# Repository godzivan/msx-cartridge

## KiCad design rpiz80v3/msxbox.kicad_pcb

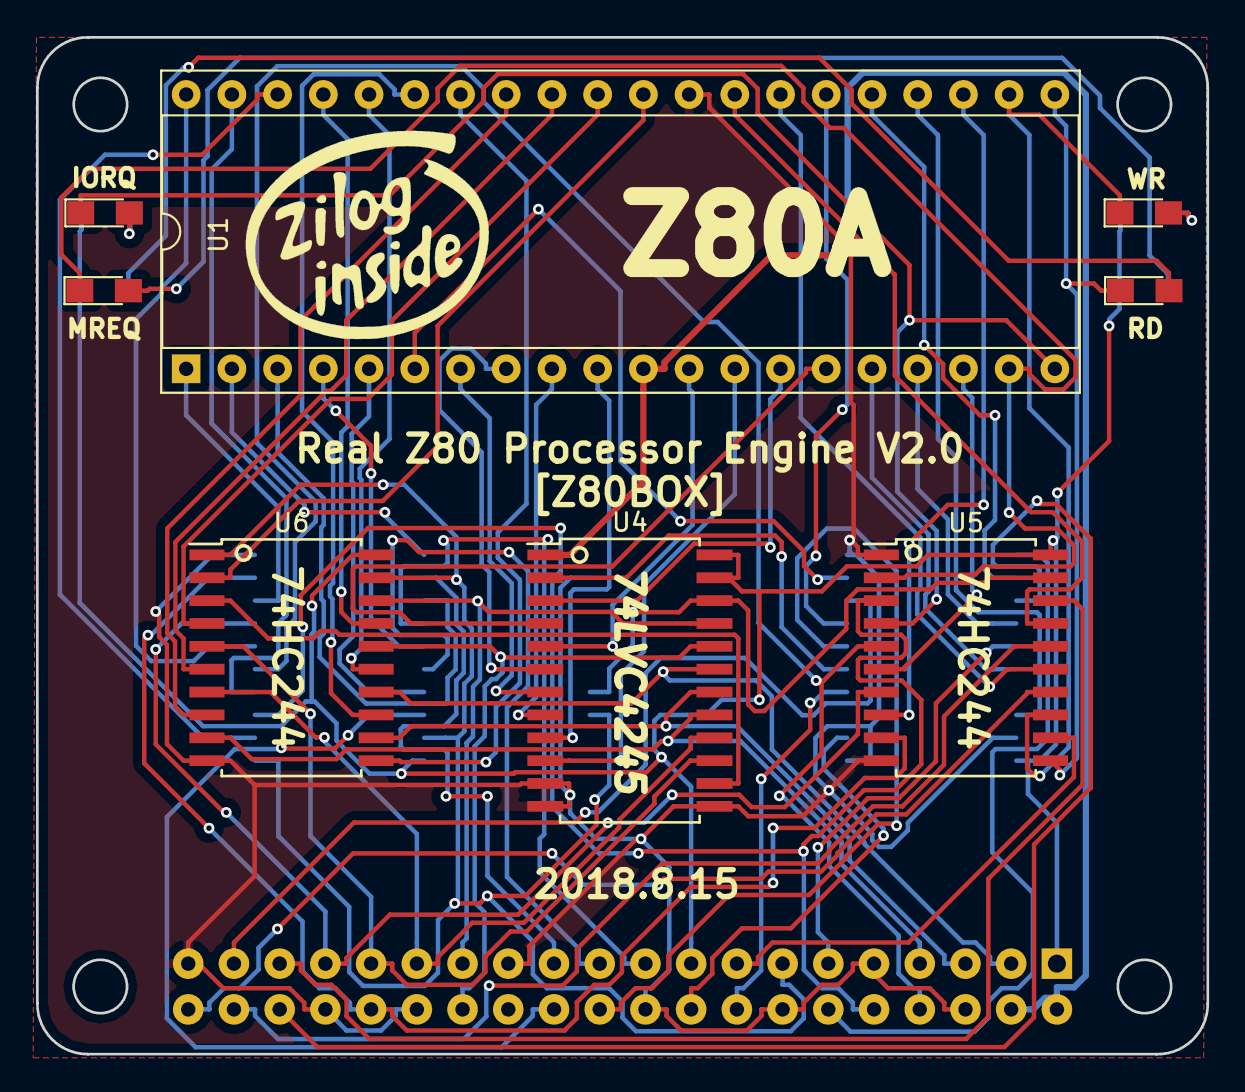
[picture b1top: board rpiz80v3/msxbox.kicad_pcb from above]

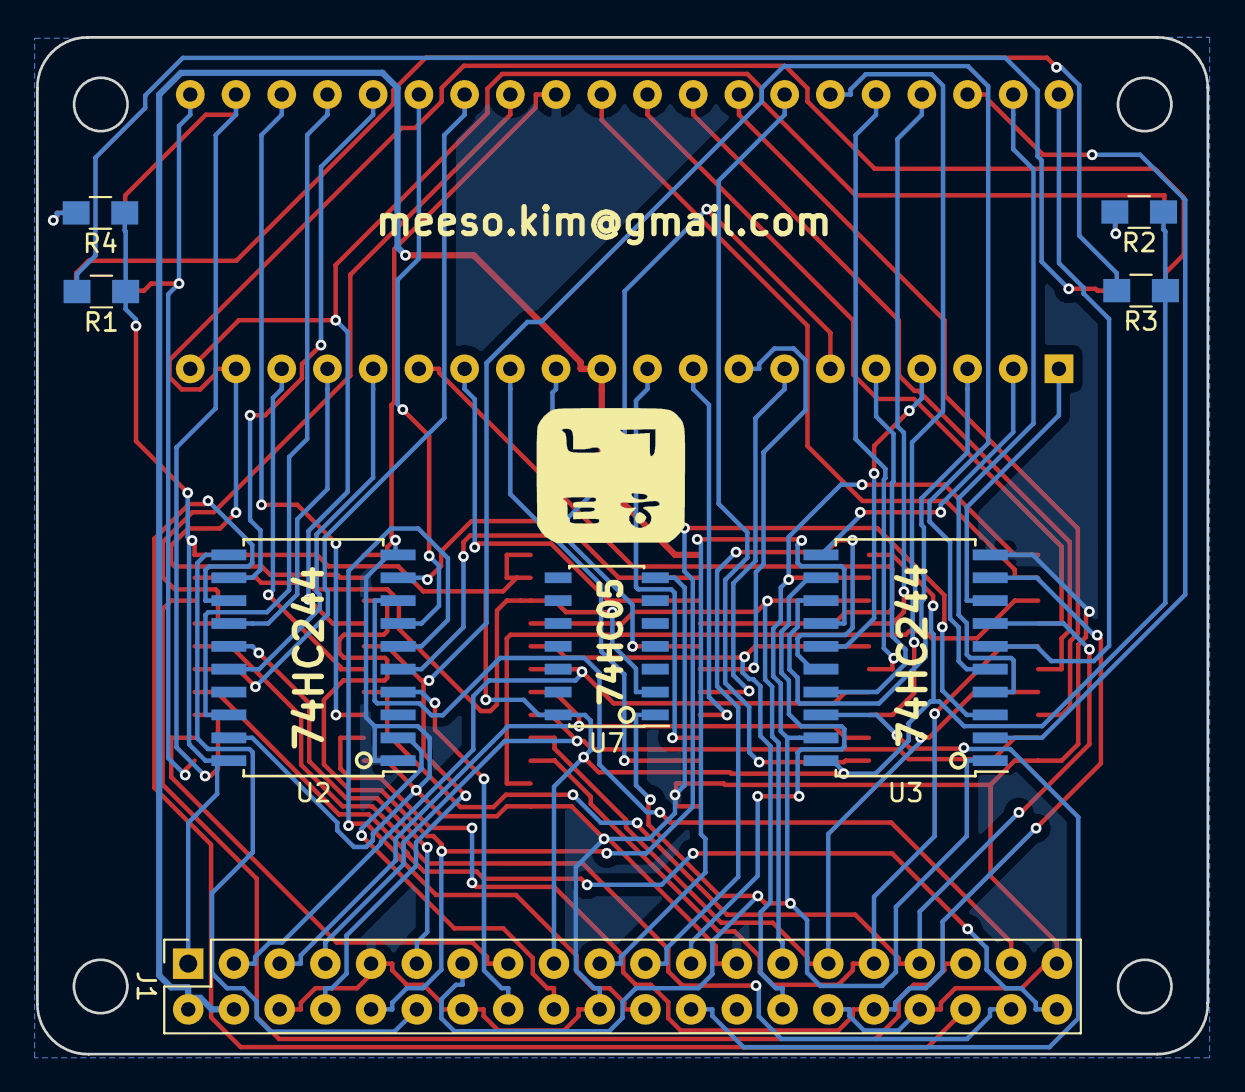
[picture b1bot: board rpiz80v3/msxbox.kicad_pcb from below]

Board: 2 copper layers, 65.0 x 56.5 mm, 16 parts (8 on the bottom side), 75 nets.

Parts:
D1, D2, D3, D4: LED_Small; LED_0805_HandSoldering
J1: Raspberry_Pi_2_3; Socket_Strip_Straight_2x20_Pitch2.54mm
R1, R2, R3, R4: R; R_0805_HandSoldering
U1: Z80CPU; DIP-40_W15.24mm_Socket
U2, U3, U5, U6: 74LS244; SOIC-20W_7.5x12.8mm_Pitch1.27mm
U4: LVC4245; SOIC-24W_7.5x15.4mm_Pitch1.27mm
U7: 74LS05; SOIC-14_3.9x8.7mm_Pitch1.27mm

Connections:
+5V: J1.2, J1.4, U1.11, U4.1
/A0: U1.30, U6.2
/A1: U1.31, U6.4
/A2: U1.32, U6.6
/A3: U1.33, U6.8
/A4: U1.34, U6.11
/A5: U1.35, U6.13
/A6: U1.36, U6.15
/A7: U1.37, U6.17
/A8: U1.38, U3.2
/A9: U1.39, U3.4
/A10: U1.40, U3.6
/A11: U1.1, U3.8
/A12: U1.2, U3.11
/A13: U1.3, U3.13
/A14: U1.4, U3.15
/A15: U1.5, U3.17
/BUSACK: U1.23, U5.8
/BUSRQ: U1.25, U2.12
/CLK: U1.6, U2.9
/D0: U1.14, U4.3
/D1: U1.15, U4.4
/D2: U1.12, U4.5
/D3: U1.8, U4.6
/D4: U1.7, U4.7
/D5: U1.9, U4.8
/D6: U1.10, U4.9
/D7: U1.13, U4.10
/DAT_DIR: U2.5, U4.2
/DAT_EN: U4.22, U5.19, U7.2
/HALT: U1.18, U5.6
/INT: U1.16, U2.16
/M1: U1.27, U5.15
/NMI: U1.17, U2.14
/RA8: J1.24, U3.18
/RA9: J1.21, U3.16
/RA10: J1.19, U3.14
/RA11: J1.23, U3.12
/RA12: J1.32, U3.9, U5.9
/RA13: J1.33, U3.7, U5.7
/RA14: J1.8, U3.5, U5.5
/RA15: J1.10, U3.3, U5.3
/RATN: J1.13, U3.1, U3.19, U6.1, U6.19, U7.1
/RC16: J1.36, U2.13
/RC17: J1.11, U2.15
/RC18: J1.12, U2.11
/RC19: J1.35, U5.18
/RC20: J1.38, U5.16
/RC21: J1.40, U5.14
/RC22: J1.15, U5.12
/RC23: J1.16, U2.4
/RC24: J1.18, U2.2
/RC25: J1.22, U2.6
/RC26: J1.37, U2.8
/RD0: J1.27, U4.21, U6.18
/RD1: J1.28, U4.20, U6.16
/RD2: J1.3, U4.19, U6.14
/RD3: J1.5, U4.18, U6.12
/RD4: J1.7, U4.17, U6.9
/RD5: J1.29, U4.16, U6.7
/RD6: J1.31, U4.15, U6.5
/RD7: U4.14, U6.3
/RESET: U1.26, U2.7
/RFSH: U1.28, U5.17
/WAIT: U1.24, U2.18
GND: J1.6, J1.9, J1.14, J1.20, J1.25, J1.30, J1.34, J1.39, U1.29, U2.1, U2.10, U2.19, U3.10, U4.11, U4.12, U4.13, U5.1, U5.10, U6.10, U7.7
IORQ: D2.1, U1.20, U5.4
MERQ: D1.1, U1.19, U5.2
unnamed: D1.2, R1.2
unnamed: D2.2, R2.2
unnamed: D3.2, R3.2
unnamed: D4.2, R4.2
RD: D3.1, U1.21, U5.11
VCC: J1.1, J1.17, R1.1, R2.1, R3.1, R4.1, U2.20, U3.20, U4.23, U4.24, U5.20, U6.20, U7.14
WR: D4.1, U1.22, U5.13

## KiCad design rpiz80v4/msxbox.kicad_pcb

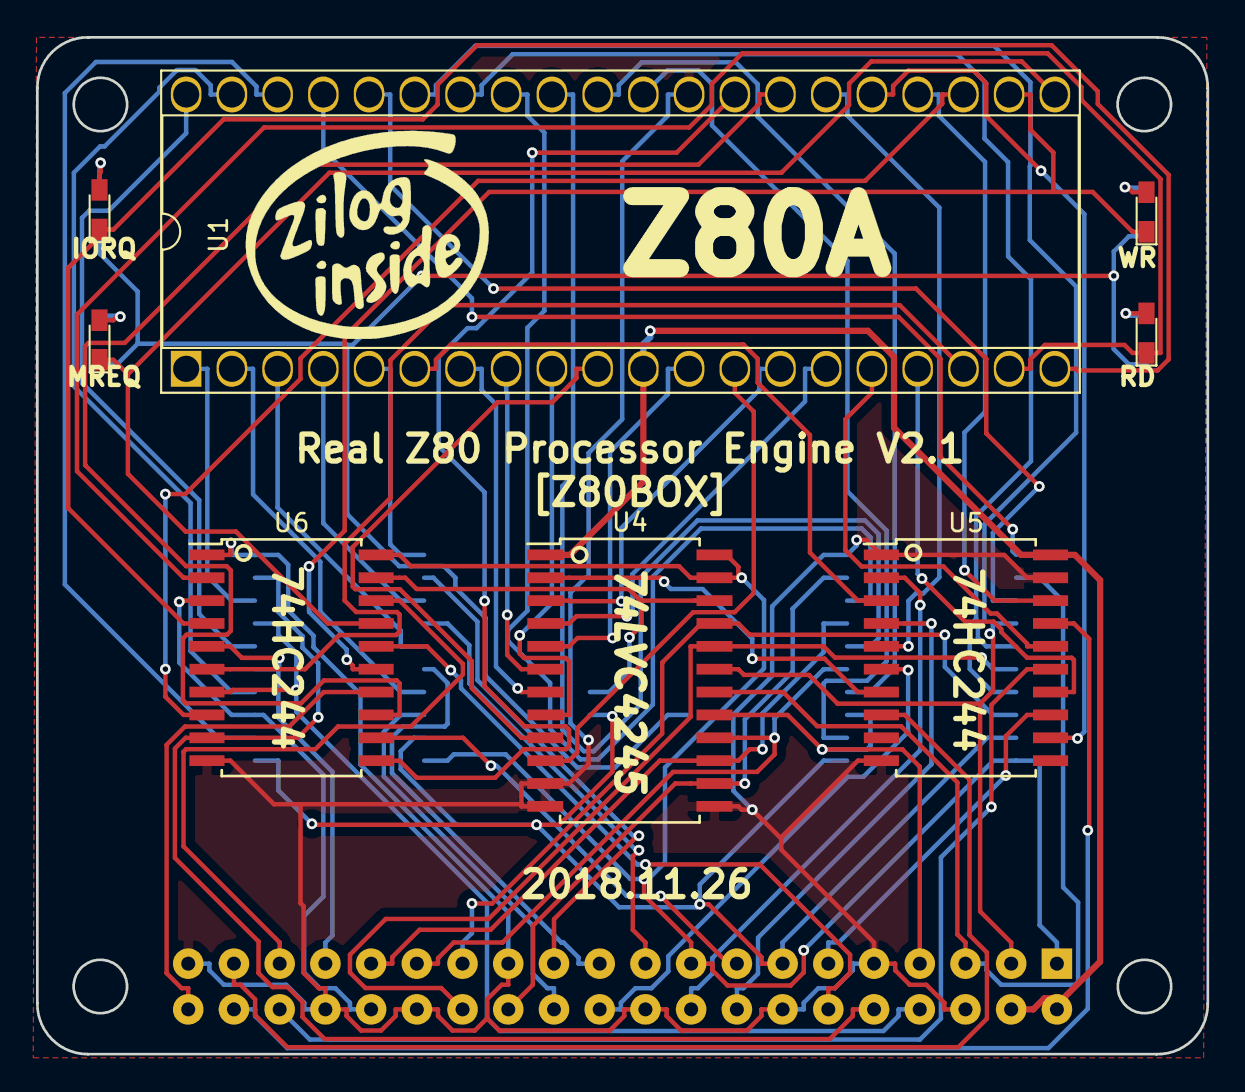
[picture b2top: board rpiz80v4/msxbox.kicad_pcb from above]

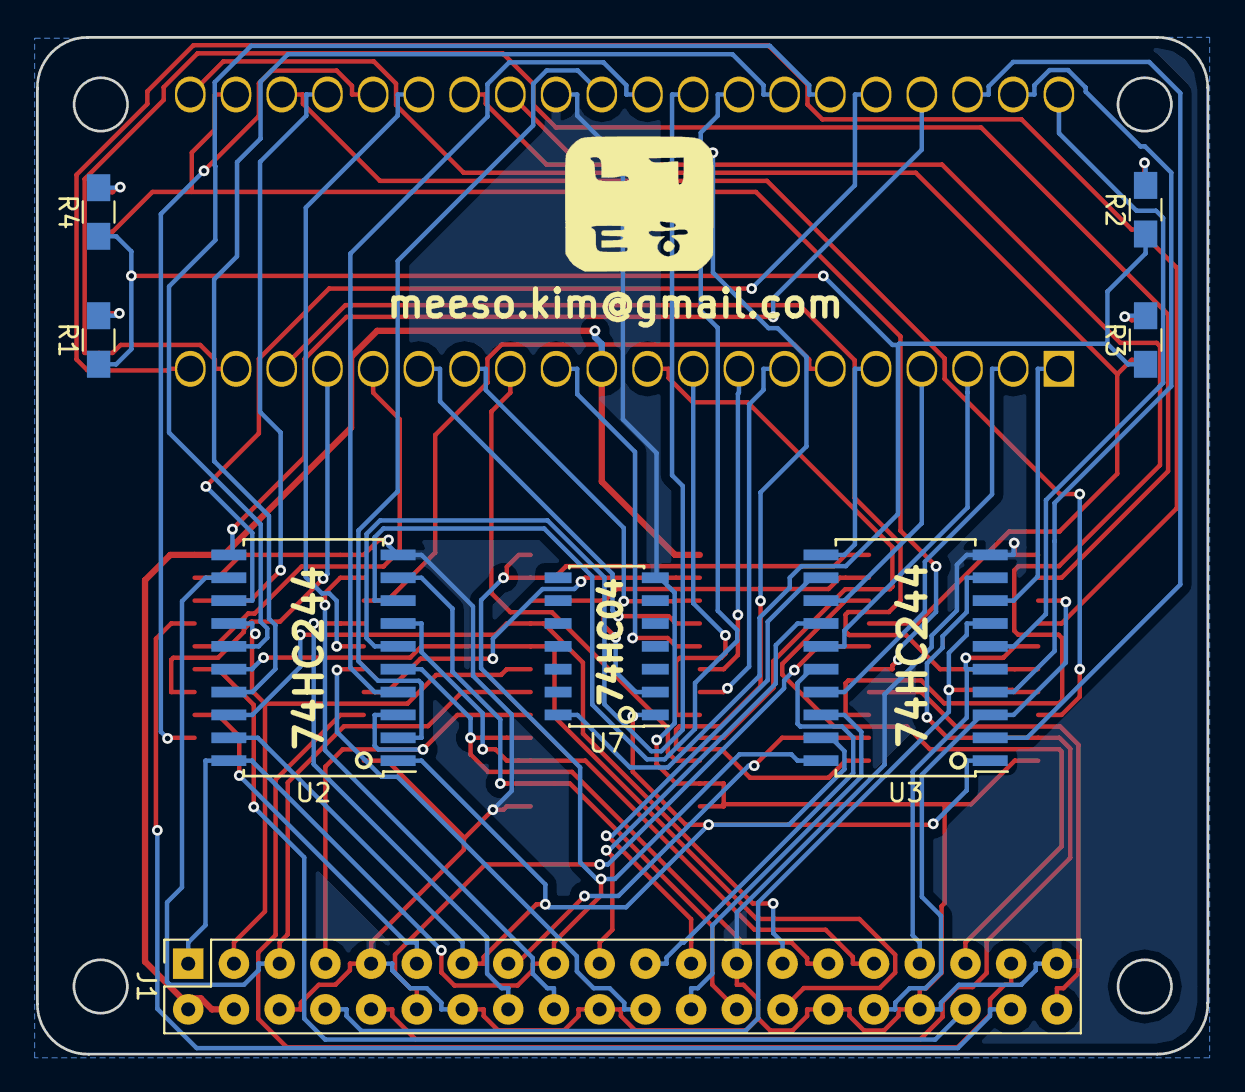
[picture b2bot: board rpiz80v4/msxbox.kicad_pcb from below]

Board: 2 copper layers, 65.0 x 56.5 mm, 17 parts (8 on the bottom side), 76 nets.

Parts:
D1, D2, D3, D4: LED_Small; LED_0603_HandSoldering
G4: LOGO; zilog_inside_logo
J1: Raspberry_Pi_2_3; Socket_Strip_Straight_2x20_Pitch2.54mm
R1, R2, R3, R4: R; R_0805_HandSoldering
U1: Z80CPU; DIP-40_W15.24mm_Socket
U2, U3, U5, U6: 74HC244; SOIC-20W_7.5x12.8mm_Pitch1.27mm
U4: LVC4245; SOIC-24W_7.5x15.4mm_Pitch1.27mm
U7: 74LS05; SOIC-14_3.9x8.7mm_Pitch1.27mm

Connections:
+5V: J1.2, J1.4, U1.11, U4.1, U5.20
/3V3: J1.1, J1.17, U2.20, U3.20, U4.23, U4.24, U6.20
/A0: U1.30, U2.2
/A1: U1.31, U2.4
/A2: U1.32, U2.6
/A3: U1.33, U2.8
/A4: U1.34, U2.17
/A5: U1.35, U2.15
/A6: U1.36, U2.13
/A7: U1.37, U2.11
/A8: U1.38, U3.2
/A9: U1.39, U3.4
/A10: U1.40, U3.6
/A11: U1.1, U3.8
/A12: U1.2, U3.17
/A13: U1.3, U3.15
/A14: U1.4, U3.13
/A15: U1.5, U3.11
/BUSACK: U1.23, U6.8
/BUSRQ: U1.25, U5.12
/CLK: U1.6, U5.3
/D0: U1.14, U4.3
/D1: U1.15, U4.4
/D2: U1.12, U4.5
/D3: U1.8, U4.6
/D4: U1.7, U4.7
/D5: U1.9, U4.8
/D6: U1.10, U4.9
/D7: U1.13, U4.10
/DAT_DIR: U4.2, U5.7
/DAT_EN: U4.22, U6.19, U7.2
/HALT: U1.18, U6.6
/INT: U1.16, U5.16
/M1: U1.27, U6.13
/NMI: U1.17, U5.14
/RA8: J1.24, U3.18
/RA9: J1.21, U3.16
/RA10: J1.19, U3.14
/RA11: J1.23, U3.12
/RA12: J1.32, U3.3, U6.3
/RA13: J1.33, U3.5, U6.5
/RA14: J1.8, U3.7, U6.7
/RA15: J1.10, U3.9, U6.9
/RATN: J1.13, U2.1, U2.19, U3.1, U3.19, U7.1
/RC16: J1.36, U5.15
/RC17: J1.11, U5.13
/RC18: J1.12, U6.16
/RC19: J1.35, U6.18
/RC20: J1.38, U5.17
/RC21: J1.40, U6.14
/RC22: J1.15, U6.12
/RC23: J1.16, U5.4
/RC24: J1.18, U5.2
/RC25: J1.22, U5.6
/RC26: J1.37, U5.8
/RD0: J1.27, U2.18, U4.21
/RD1: J1.28, U2.16, U4.20
/RD2: J1.3, U2.14, U4.19
/RD3: J1.5, U2.12, U4.18
/RD4: J1.7, U2.3, U4.17
/RD5: J1.29, U2.5, U4.16
/RD6: J1.31, U2.7, U4.15
/RD7: J1.26, U2.9, U4.14
/RESET: U1.26, U5.5
/RFSH: U1.28, U6.11
/WAIT: U1.24, U5.18
GND: J1.6, J1.9, J1.14, J1.20, J1.25, J1.30, J1.34, J1.39, U1.29, U2.10, U3.10, U4.11, U4.12, U4.13, U5.1, U5.10, U5.19, U6.1, U6.10, U7.7
IORQ: D2.1, U1.20, U6.4
MERQ: D1.1, U1.19, U6.2
unnamed: D1.2, R1.2
unnamed: D2.2, R2.2
unnamed: D3.2, R3.2
unnamed: D4.2, R4.2
RD: D3.1, U1.21, U6.17
VCC: R1.1, R2.1, R3.1, R4.1, U7.14
WR: D4.1, U1.22, U6.15

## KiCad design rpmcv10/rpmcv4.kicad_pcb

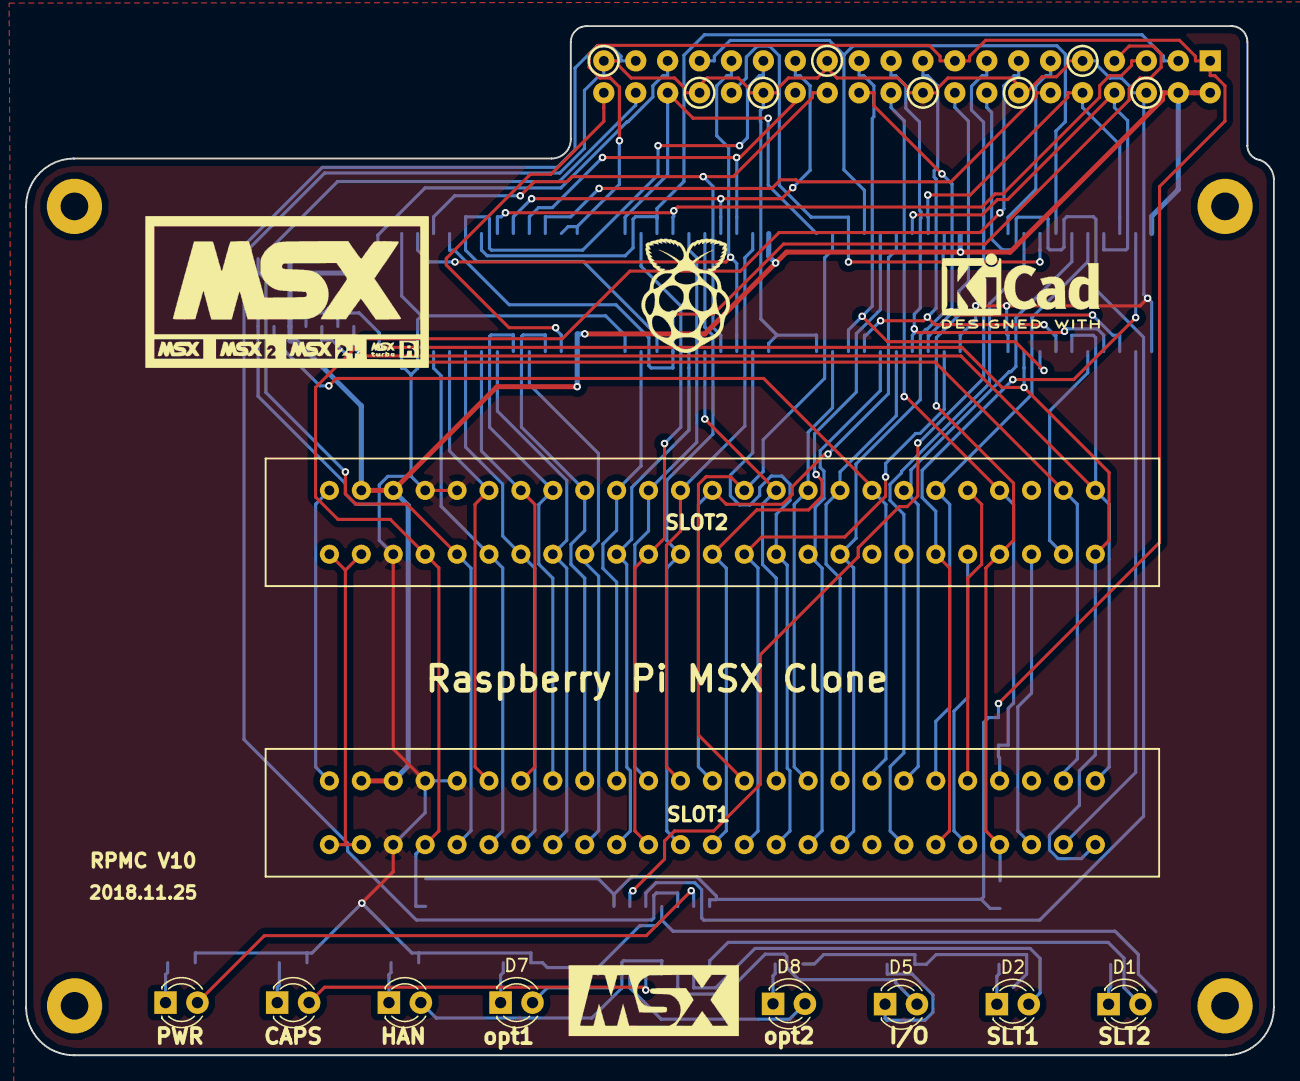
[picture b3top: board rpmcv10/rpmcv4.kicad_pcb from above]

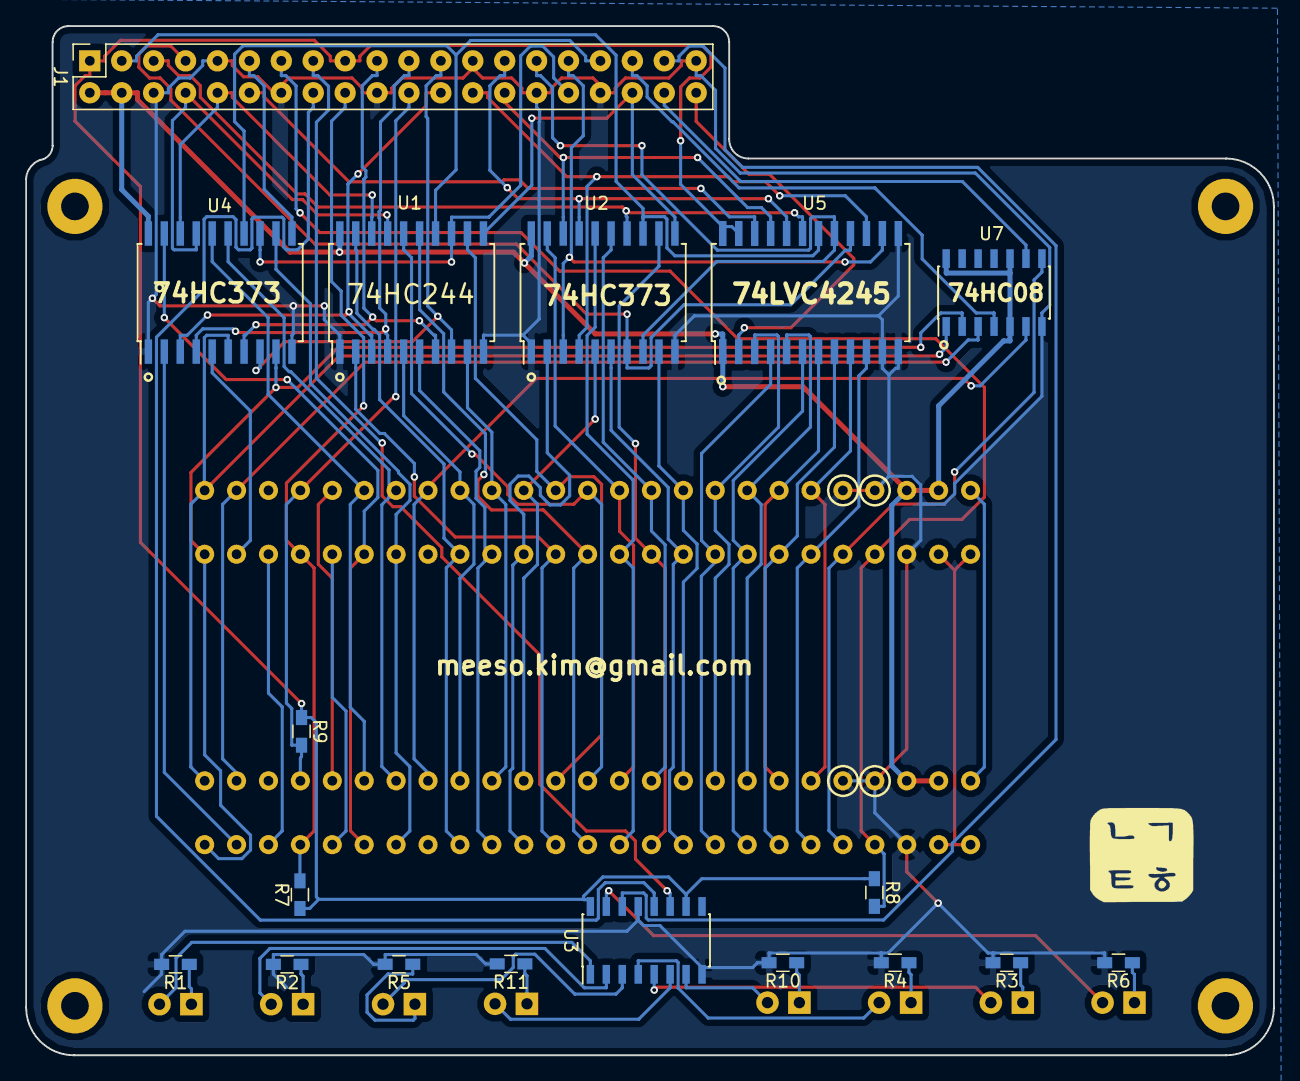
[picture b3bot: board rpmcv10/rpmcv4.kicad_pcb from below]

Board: 2 copper layers, 99.3 x 81.9 mm, 36 parts (19 on the bottom side), 87 nets.

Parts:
D1, D2, D3, D4, D5, D6, D7, D8: LED; LED_D3.0mm
G1: LOGO; raspberry_pi_logo
G2: LOGO; msx_msx2_msx+logo
G3: KiCad-Logo2_6mm_SilkScreen
GMSX: LOGO
H1, H2, H3, H4: MountingHole_2.2mm_M2_Pad
J1: RPi_GPIO; Socket_Strip_Straight_2x20_Pitch2.54mm
P1, P2: CONN_02X25; MSX_SLOT
R1, R2, R3, R4, R5, R6, R7, R8, R9, R10, R11: R; R_0603_HandSoldering
U1, U2, U4: 74LS373; SOIC-20W_7.5x12.8mm_Pitch1.27mm
U3: 74HC595; SOIC-16_3.9x9.9mm_Pitch1.27mm
U5: LVC4245; SOIC-24W_7.5x15.4mm_Pitch1.27mm
U7: 74LS08; SOIC-14_3.9x8.7mm_Pitch1.27mm

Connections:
+3V3: J1.1, J1.17, R7.1, R8.1, R9.1, U3.10, U3.16, U5.23, U5.24
+5V: J1.2, J1.4, P1.45, P1.47, P2.45, P2.47, U1.20, U2.20, U4.20, U5.1, U7.5, U7.10, U7.14
/+12V: P1.48, P1.50, P2.48, P2.50
/A0: P1.28, P2.28, U2.16
/A1: P1.27, P2.27, U2.19
/A2: P1.30, P2.30, U2.12
/A3: P1.29, P2.29, U2.15
/A4: P1.32, P2.32, U2.6
/A5: P1.31, P2.31, U2.9
/A6: P1.22, P2.22, U2.2
/A7: P1.21, P2.21, U2.5
/A8: P1.24, P2.24, U1.2
/A9: P1.17, P2.17, U1.5
/A10: P1.20, P2.20, U1.6
/A11: P1.19, P2.19, U1.9
/A12: P1.23, P2.23, U1.12
/A13: P1.26, P2.26, U1.15
/A14: P1.25, P2.25, U1.16
/A15: P1.18, P2.18, U1.19
/BUSDIR: P1.10, P2.10
/CLK: P1.42, P2.42, U7.8
/CS1: P1.1, P2.1, U4.6, U7.1
/CS2: P1.2, P2.2, U4.9, U7.2
/CS12: P1.3, P2.3, U7.3
/D0: P1.34, P2.34, U5.4
/D1: P1.33, P2.33, U5.3
/D2: P1.36, P2.36, U5.6
/D3: P1.35, P2.35, U5.5
/D4: P1.38, P2.38, U5.8
/D5: P1.37, P2.37, U5.7
/D6: P1.40, P2.40, U5.10
/D7: P1.39, P2.39, U5.9
/INT: J1.18, P1.8, P2.8, R7.2
/IORQ: P1.11, P2.11, U4.16
/M1: P1.9, P2.9
/MREQ: P1.12, P2.12, U4.19
/RA8: J1.24, U1.3, U4.3
/RA9: J1.21, U1.4, U4.4
/RA10: J1.19, U1.7, U4.7
/RA11: J1.23, U1.8, U4.8
/RA12: J1.32, U1.13, U4.13
/RA13: J1.33, U1.14, U4.14
/RA14: J1.8, U1.17, U4.17
/RA15: J1.10, U1.18, U4.18
/RC16: J1.36, U1.11, U2.11
/RC17: J1.11, U4.11
/RC18: J1.12, U5.22
/RC19: J1.35, U7.4
/RC20: J1.38, U7.9
/RC21: J1.40, U5.2
/RC22: J1.15, U3.11
/RC23: J1.16, U3.12
/RC25: J1.22, P1.7, P2.7, R9.2
/RC26: J1.37, U3.14
/RC27: J1.13, P1.44, P2.44, R8.2
/RD: P1.14, P2.14, U4.12
/RD0: J1.27, U2.17, U5.20
/RD1: J1.28, U2.18, U5.21
/RD2: J1.3, U2.13, U5.18
/RD3: J1.5, U2.14, U5.19
/RD4: J1.7, U2.7, U5.16
/RD5: J1.29, U2.8, U5.17
/RD6: J1.31, U2.3, U5.14
/RD7: J1.26, U2.4, U5.15
/RESET: P1.15, P2.15, U7.6
/RFSH: P1.6, P2.6
/SLTSL1: P1.4, U4.2
/SLTSL2: P2.4, U4.5
/SNDIN: P1.49, P2.49
/WR: P1.13, P2.13, U4.15
GND: J1.6, J1.9, J1.14, J1.20, J1.25, J1.30, J1.34, J1.39, P1.41, P1.43, P1.46, P2.41, P2.43, P2.46, R1.2, R2.2, R3.2, R4.2, R5.2, R6.2, R10.2, R11.2, U1.1, U1.10, U2.1, U2.10, U3.8, U3.13, U4.1, U4.10, U5.11, U5.12, U5.13, U7.7
unnamed: D1.1, R1.1
unnamed: D1.2, U3.1
unnamed: D2.1, R2.1
unnamed: D2.2, U3.2
unnamed: D3.1, R3.1
unnamed: D3.2, U3.5
unnamed: D4.1, R4.1
unnamed: D4.2, U3.4
unnamed: D5.1, R5.1
unnamed: D5.2, U3.3
unnamed: D6.1, R6.1
unnamed: D6.2, U3.15
unnamed: D7.1, R10.1
unnamed: D7.2, U3.7
unnamed: D8.1, R11.1
unnamed: D8.2, U3.6

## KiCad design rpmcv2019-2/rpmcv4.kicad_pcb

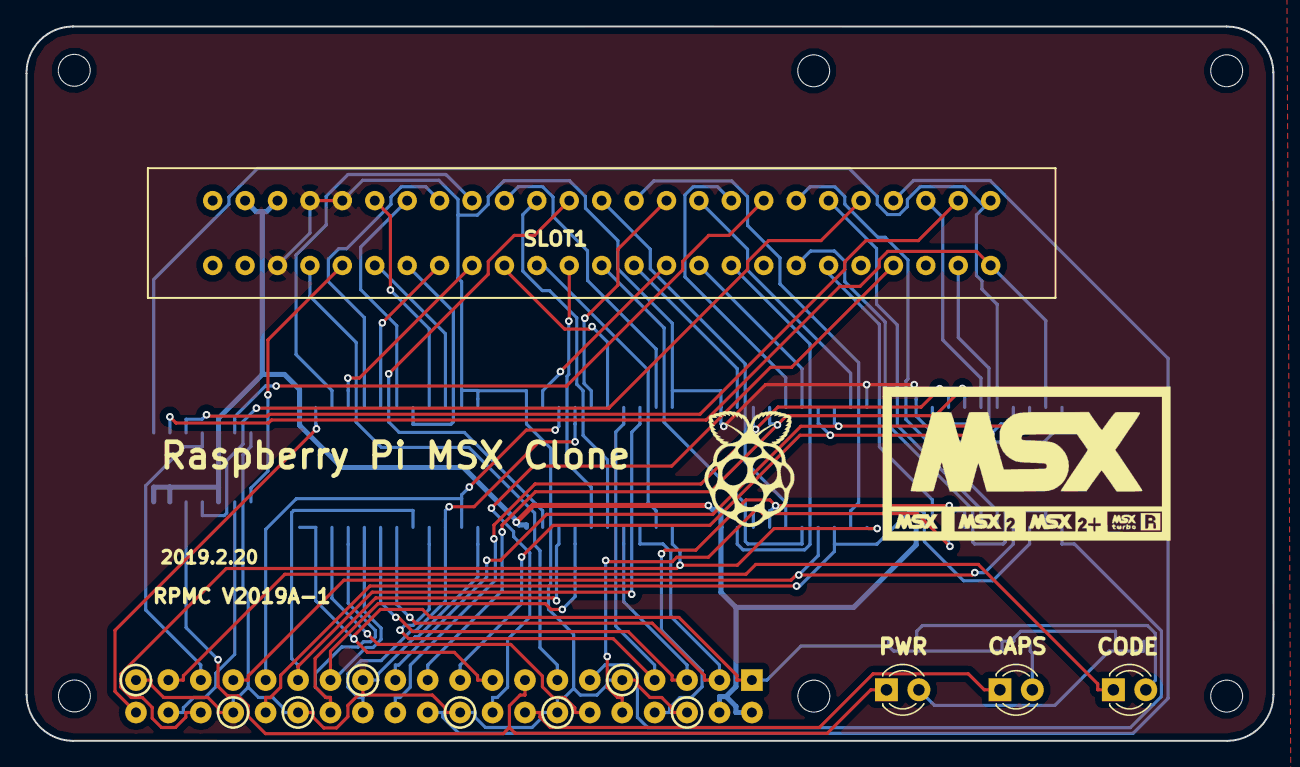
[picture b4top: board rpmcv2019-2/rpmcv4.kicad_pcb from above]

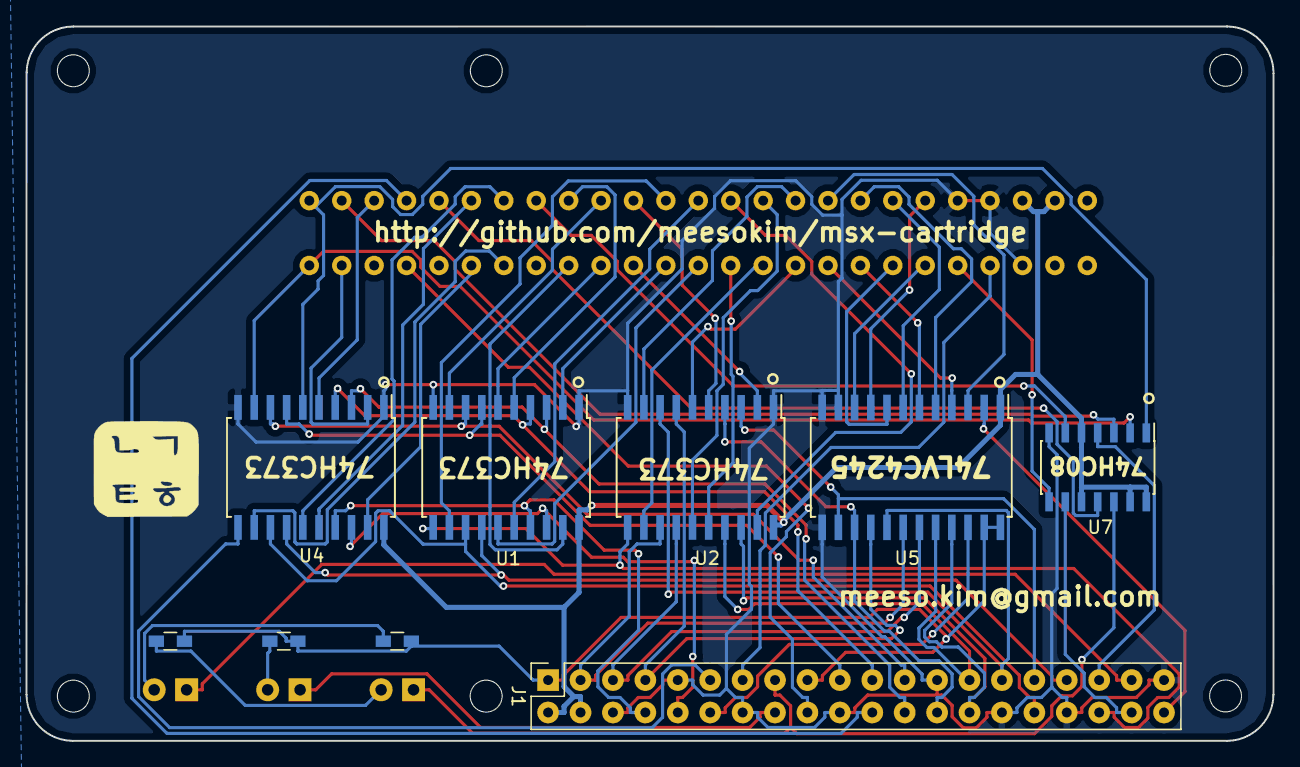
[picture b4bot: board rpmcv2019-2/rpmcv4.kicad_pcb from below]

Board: 2 copper layers, 97.7 x 56.0 mm, 21 parts (9 on the bottom side), 70 nets.

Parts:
D1, D2, D3: LED; LED_D3.0mm
G1: LOGO; raspberry_pi_logo
G2: LOGO; msx_msx2_msx+logo
J1: RPi_GPIO; Socket_Strip_Straight_2x20_Pitch2.54mm
P1: CONN_02X25; MSX_SLOT
R1, R2, R3: R; R_0603_HandSoldering
REF1, REF2, REF3, REF4, REF5, REF6: MountingHole_2.5mm
U1, U2, U4: 74LS373; SOIC-20W_7.5x12.8mm_Pitch1.27mm
U5: LVC4245; SOIC-24W_7.5x15.4mm_Pitch1.27mm
U7: 74LS08; SOIC-14_3.9x8.7mm_Pitch1.27mm

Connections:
+3V3: J1.1, J1.17, R1.1, R2.1, R3.1, U5.23, U5.24
+5V: J1.2, J1.4, P1.45, P1.47, U1.20, U2.20, U4.20, U5.1, U7.5, U7.10, U7.13, U7.14
/A0: P1.28, U2.16
/A1: P1.27, U2.19
/A2: P1.30, U2.12
/A3: P1.29, U2.15
/A4: P1.32, U2.6
/A5: P1.31, U2.9
/A6: P1.22, U2.2
/A7: P1.21, U2.5
/A8: P1.24, U1.2
/A9: P1.17, U1.5
/A10: P1.20, U1.6
/A11: P1.19, U1.9
/A12: P1.23, U1.12
/A13: P1.26, U1.15
/A14: P1.25, U1.16
/A15: P1.18, U1.19
/CLK: P1.42, U7.8
/CS1: P1.1, U4.6, U7.1
/CS2: P1.2, U4.9, U7.2
/CS12: P1.3, U7.3
/D0: P1.34, U5.4
/D1: P1.33, U5.3
/D2: P1.36, U5.6
/D3: P1.35, U5.5
/D4: P1.38, U5.8
/D5: P1.37, U5.7
/D6: P1.40, U5.10
/D7: P1.39, U5.9
/INT: J1.18, P1.8
/IORQ: P1.11, U4.16
/M1: P1.9, U7.11
/MREQ: P1.12, U4.19
/RA8: J1.24, U1.3, U4.3
/RA9: J1.21, U1.4, U4.4
/RA10: J1.19, U1.7, U4.7
/RA11: J1.23, U1.8, U4.8
/RA12: J1.32, U1.13, U4.13
/RA13: J1.33, U1.14, U4.14
/RA14: J1.8, U1.17, U4.17
/RA15: J1.10, U1.18, U4.18
/RC16: J1.36, U1.11, U2.11
/RC17: J1.11, U4.11
/RC18: J1.12, U5.22
/RC19: J1.35, U7.4
/RC20: J1.38, U7.9
/RC21: J1.40, U5.2
/RC22: D1.1, J1.15, U7.12
/RC23: D2.1, J1.16
/RC25: J1.22, P1.7
/RC26: D3.1, J1.37
/RC27: J1.13, P1.44
/RD: P1.14, U4.12
/RD0: J1.27, U2.17, U5.20
/RD1: J1.28, U2.18, U5.21
/RD2: J1.3, U2.13, U5.18
/RD3: J1.5, U2.14, U5.19
/RD4: J1.7, U2.7, U5.16
/RD5: J1.29, U2.8, U5.17
/RD6: J1.31, U2.3, U5.14
/RD7: J1.26, U2.4, U5.15
/RESET: P1.15, U7.6
/SLTSL1: P1.4, U4.2
/WR: P1.13, U4.15
/WR_EXT: P1.5, U4.5
GND: J1.6, J1.9, J1.14, J1.20, J1.25, J1.30, J1.34, J1.39, P1.41, P1.43, P1.46, U1.1, U1.10, U2.1, U2.10, U4.1, U4.10, U5.11, U5.12, U5.13, U7.7
unnamed: D1.2, R3.2
unnamed: D2.2, R2.2
unnamed: D3.2, R1.2

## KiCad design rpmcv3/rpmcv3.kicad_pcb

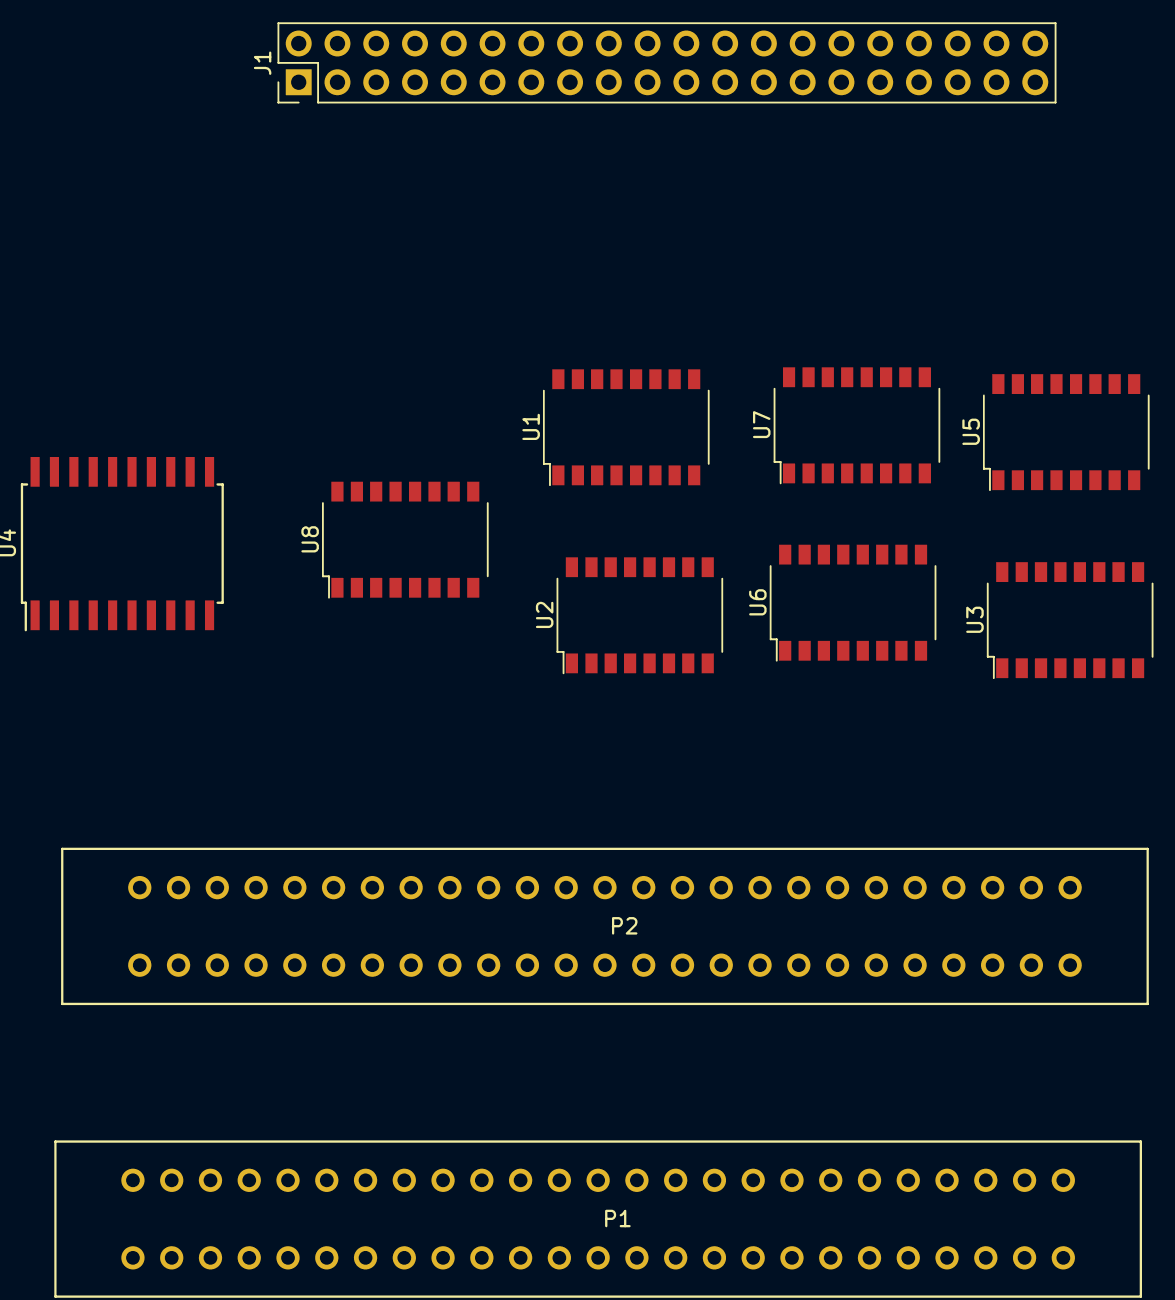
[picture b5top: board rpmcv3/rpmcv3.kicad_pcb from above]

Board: 2 copper layers, 11 parts (0 on the bottom side), 2 nets, no tracks yet.

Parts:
J1: RPi_GPIO; Pin_Header_Straight_2x20_Pitch2.54mm
P1, P2: CONN_02X25; MSX_SLOT
U1, U2, U3, U5, U6, U7, U8: 74LS595; SOP-16_4.4x10.4mm_Pitch1.27mm
U4: 74LS245; SOIC-20W_7.5x12.8mm_Pitch1.27mm

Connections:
GND: U1.8, U2.8, U3.8, U4.10, U5.8, U6.8, U7.8, U8.8
VCC: U1.16, U2.16, U3.16, U4.20, U5.16, U6.16, U7.16, U8.16

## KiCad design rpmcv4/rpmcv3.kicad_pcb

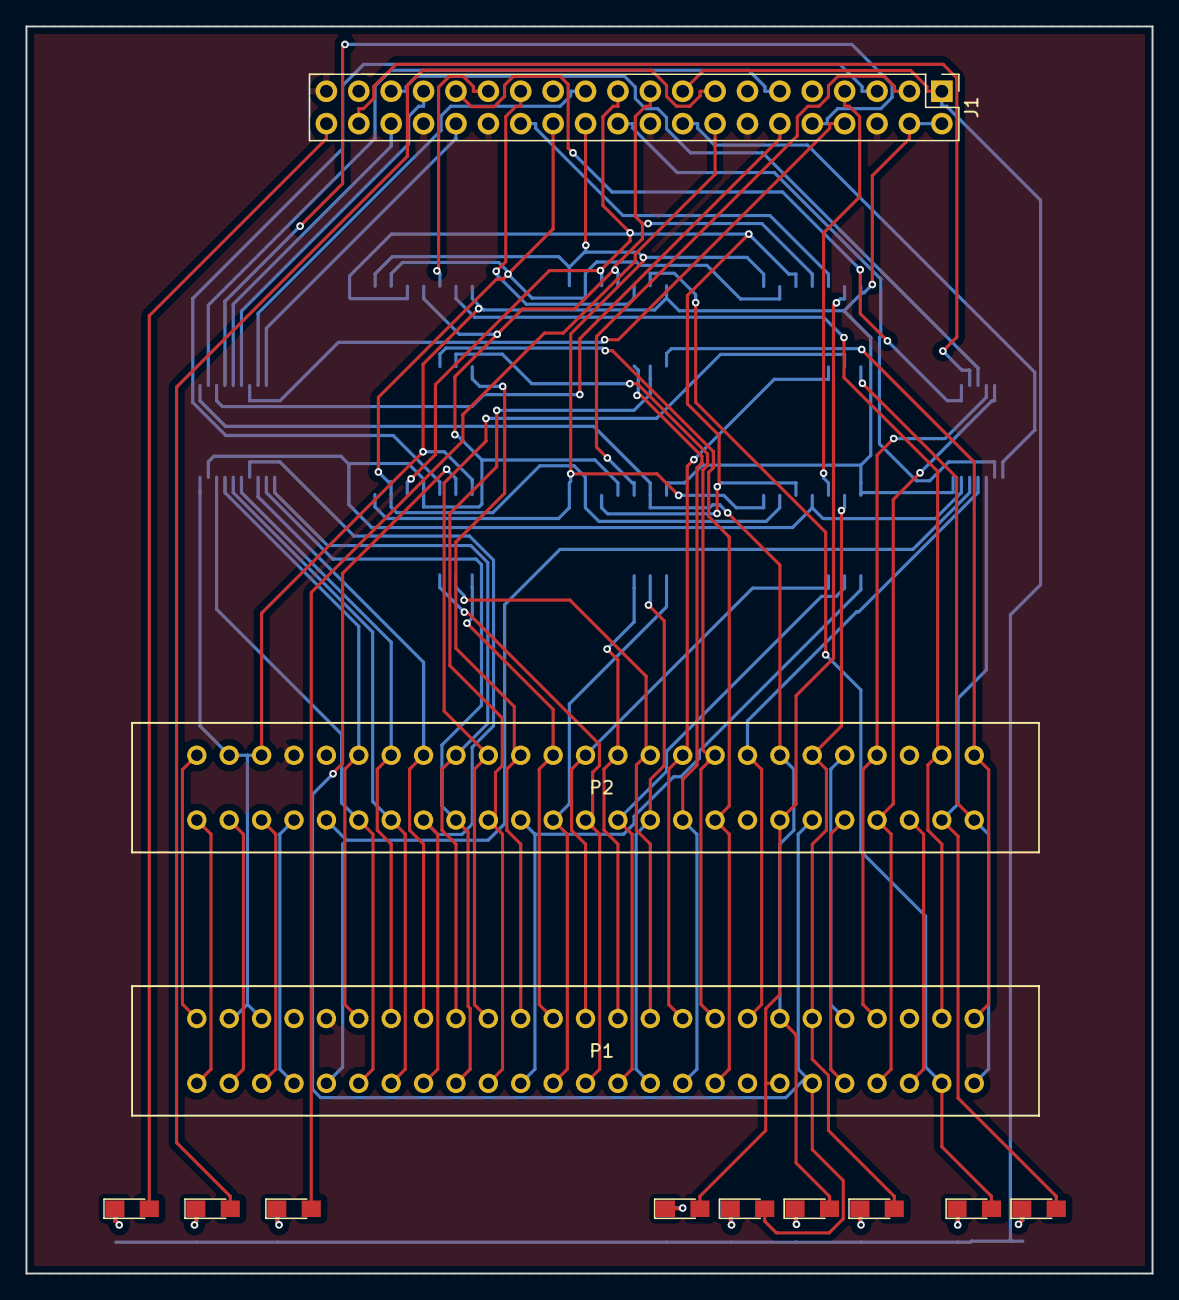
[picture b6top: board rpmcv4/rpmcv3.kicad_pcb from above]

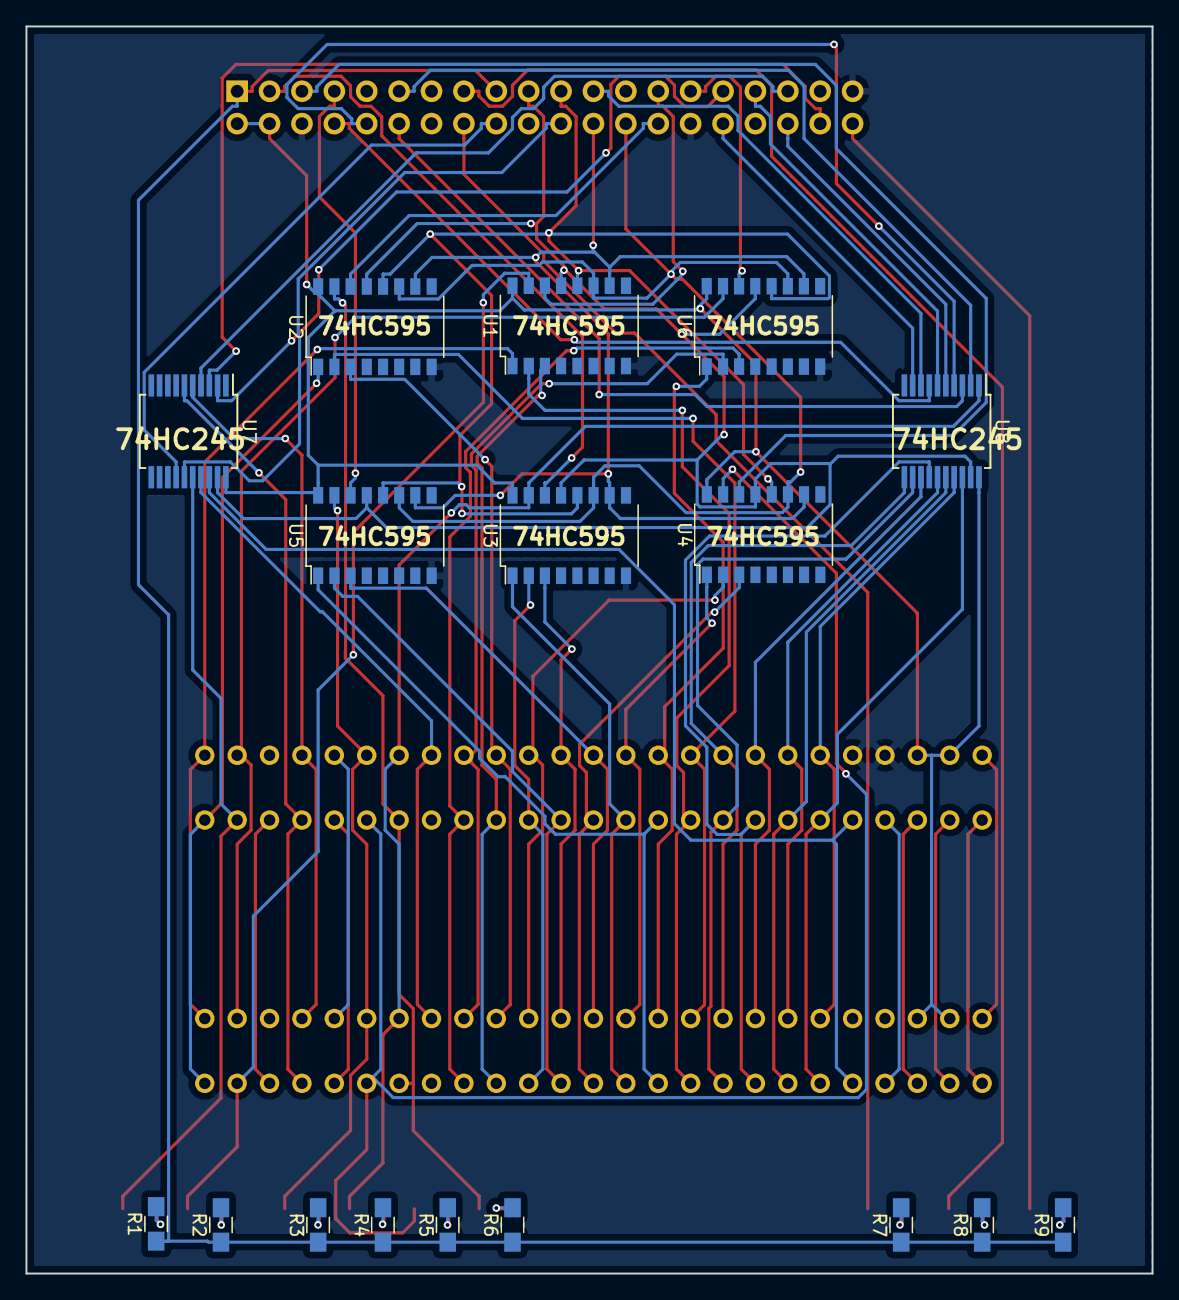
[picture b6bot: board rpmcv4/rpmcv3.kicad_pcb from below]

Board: 2 copper layers, 88.3 x 97.8 mm, 29 parts (17 on the bottom side), 83 nets.

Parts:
D1, D2, D3, D4, D5, D6, D7, D8, D9: Led_Small; LED_0805_HandSoldering
J1: RPi_GPIO; Pin_Header_Straight_2x20_Pitch2.54mm
P1, P2: CONN_02X25; MSX_SLOT
R1, R2, R3, R4, R5, R6, R7, R8, R9: R; R_0805_HandSoldering
U1, U2, U3, U4, U5, U6: 74LS595; SOP-16_4.4x10.4mm_Pitch1.27mm
U7, U8: 74LS245; SSOP-20_5.3x7.2mm_Pitch0.65mm

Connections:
+3V3: J1.1, J1.17, R1.1, R2.1, R3.1, R4.1, R5.1, R6.1, R7.1, R8.1, R9.1
+5V: J1.2, J1.4, P1.45, P1.47, P2.45, P2.47, U1.16, U2.16, U3.16, U4.16, U5.16, U6.16, U7.20, U8.20
/+12V: P1.48, P2.48
/+V12: P1.50, P2.50
/A0: P1.28, P2.28, U3.1
/A1: P1.27, P2.27, U4.1
/A2: P1.30, P2.30, U5.1
/A3: P1.29, P2.29, U6.1
/A4: P1.32, P2.32, U1.2
/A5: P1.31, P2.31, U2.2
/A6: P1.22, P2.22, U3.2
/A7: P1.21, P2.21, U4.2
/A8: P1.24, P2.24, U5.2
/A9: P1.17, P2.17, U6.2
/A10: P1.20, P2.20, U1.3
/A11: P1.19, P2.19, U2.3
/A12: P1.23, P2.23, U3.3
/A13: P1.26, P2.26, U4.3
/A14: P1.25, P2.25, U5.3
/A15: P1.18, P2.18, U6.3
/BUSDIR: P1.10, P2.10
/CAPS: D8.2, J1.15
/CLK: P1.42, P2.42, U7.18
/CS1: P1.1, P2.1, U1.1
/CS2: P1.2, P2.2, U2.1
/CS12: P1.3, P2.3, U6.15
/D0: P1.34, P2.34, U8.12
/D1: P1.33, P2.33, U8.11
/D2: P1.36, P2.36, U8.14
/D3: P1.35, P2.35, U8.13
/D4: P1.38, P2.38, U8.16
/D5: P1.37, P2.37, U8.15
/D6: P1.40, P2.40, U8.18
/D7: P1.39, P2.39, U8.17
/HAN: D7.2, J1.16
/INT: P1.8, P2.8, U7.6
/IORQ: D3.2, P1.11, P2.11, U5.15
/LATCH: J1.21, U1.12, U2.12, U3.12, U4.12, U5.12, U6.12
/M1: P1.9, P2.9
/MOSI0: J1.27, U1.14
/MOSI1: J1.28, U2.14
/MOSI2: J1.3, U3.14
/MOSI3: J1.5, U4.14
/MOSI4: J1.7, U5.14
/MOSI5: J1.29, U6.14
/MREQ: D5.2, P1.12, P2.12, U4.15
/OE: J1.19, U1.13, U2.13, U3.13, U4.13, U5.13, U6.13, U7.19, U8.19
/PWR: D9.2, J1.40
/RCLK: J1.31, U7.2
/RD: D6.2, P1.14, P2.14, U2.15
/RD0: J1.23, U8.8
/RD1: J1.32, U8.9
/RD2: J1.33, U8.6
/RD3: J1.8, U8.7
/RD4: J1.10, U8.4
/RD5: J1.36, U8.5
/RD6: J1.11, U8.2
/RD7: J1.12, U8.3
/RESET: P1.15, P2.15, U7.17
/RFSH: P1.6, P2.6
/RINT: J1.18, U7.14
/RRESET: J1.38, U7.3
/RSLTSL3: J1.35, U7.4
/RWAIT: J1.22, U7.15
/SLTSL1: D2.2, P1.4, U1.15
/SLTSL3: D1.2, P2.4, U7.16
/SNDIN: P1.49, P2.49
/SRCLK: J1.26, U1.11, U2.11, U3.11, U4.11, U5.11, U6.11
/SRCLR: J1.24, U1.10, U2.10, U3.10, U4.10, U5.10, U6.10
/SW1: P1.44, P2.44
/SW2: P1.46, P2.46
/WAIT: P1.7, P2.7, U7.5
/WR: D4.2, P1.13, P2.13, U3.15, U8.1
GND: J1.6, J1.9, J1.14, J1.20, J1.25, J1.30, J1.34, J1.39, P1.41, P1.43, P2.41, P2.43, U1.8, U2.8, U3.8, U4.8, U5.8, U6.8, U7.1, U7.10, U8.10
unnamed: D1.1, R1.2
unnamed: D2.1, R2.2
unnamed: D3.1, R3.2
unnamed: D4.1, R4.2
unnamed: D5.1, R5.2
unnamed: D6.1, R6.2
unnamed: D7.1, R7.2
unnamed: D8.1, R8.2
unnamed: D9.1, R9.2
